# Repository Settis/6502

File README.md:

This was started as a self-educational project.
To understand how computer works I decided to create one.
The main rule here is that I should understand each bit, each connection.
I try to build it from scratch as much as possible.

I've started with a 6502 compatible CPU in Logisim [avaialbe here](/logisim/README.md).

Currently, I'm trying to build the real one around 65c816 CPU. 
As an example of how it looks you can see it working with three character displays running Wozmon:

Finally I'm able to connect all peripherals at once:

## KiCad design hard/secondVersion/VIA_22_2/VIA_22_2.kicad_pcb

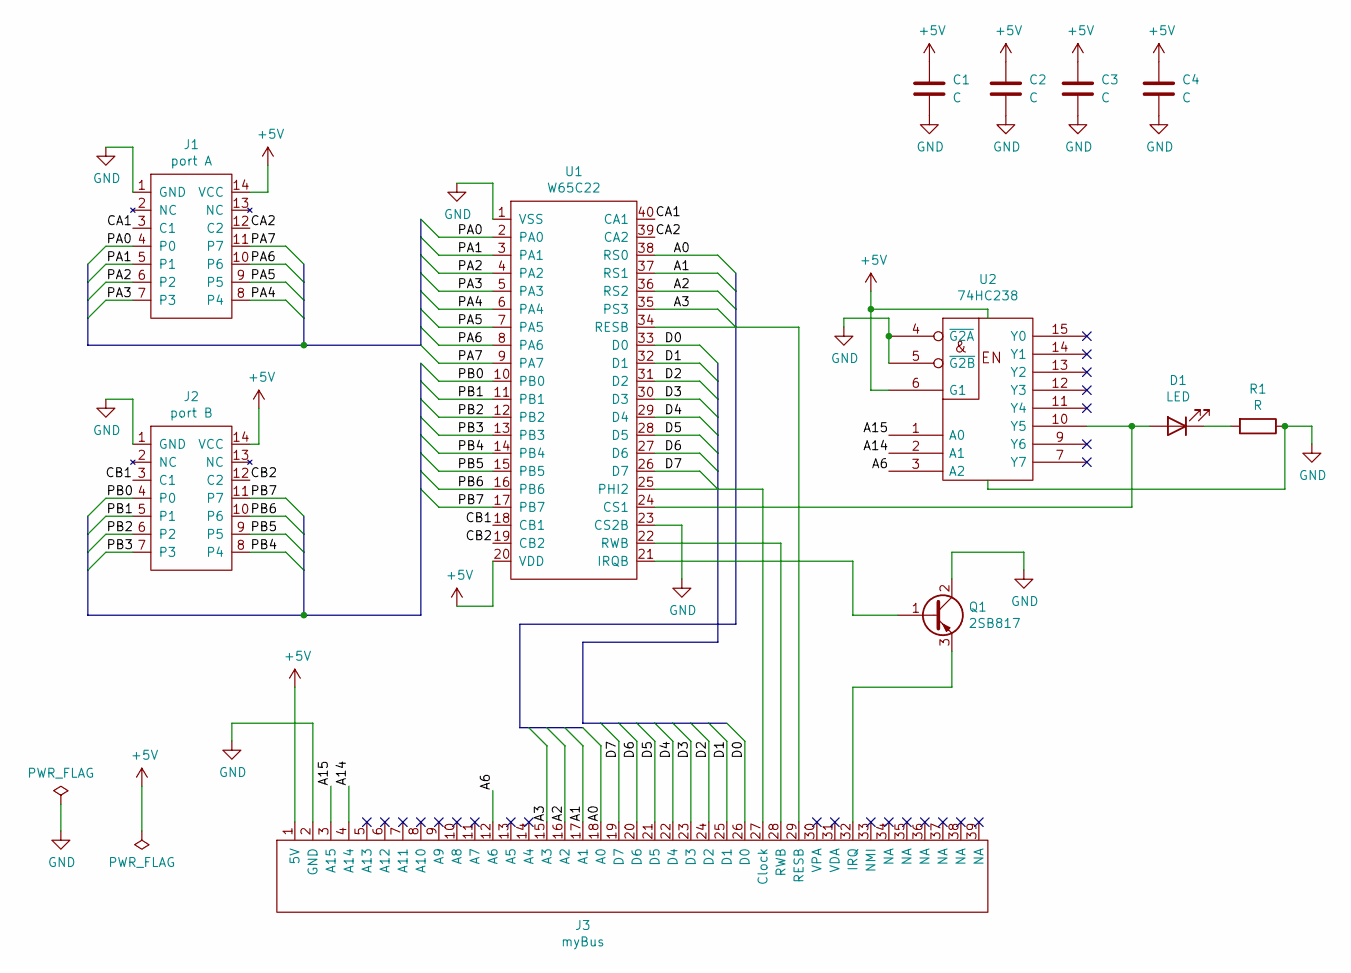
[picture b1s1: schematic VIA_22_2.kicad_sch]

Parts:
C1, C2, C3, C4: C; C_Disc_D4.3mm_W1.9mm_P5.00mm
D1: LED; LED_D5.0mm
J1: port A; DIP-14_W7.62mm_Socket
J2: port B; DIP-14_W7.62mm_Socket
J3: myBus; PinHeader_1x39_P2.54mm_Horizontal
Q1: 2SB817; TO-126-3_Vertical
R1: R; R_Axial_DIN0207_L6.3mm_D2.5mm_P15.24mm_Horizontal
U1: W65C22; DIP-40_W15.24mm_Socket
U2: 74HC238; DIP-16_W7.62mm_Socket

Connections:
/A0: J3.18 (A0), U1.38 (RS0)
/A1: J3.17 (A1), U1.37 (RS1)
/A2: J3.16 (A2), U1.36 (RS2)
/A3: J3.15 (A3), U1.35 (PS3)
/A6: J3.12 (A6), U2.3 (A2)
/A14: J3.4 (A14), U2.2 (A1)
/A15: J3.3 (A15), U2.1 (A0)
/CA1: J1.3 (C1), U1.40 (CA1)
/CA2: J1.12 (C2), U1.39 (CA2)
/CB1: J2.3 (C1), U1.18 (CB1)
/CB2: J2.12 (C2), U1.19 (CB2)
/D0: J3.26 (D0), U1.33 (D0)
/D1: J3.25 (D1), U1.32 (D1)
/D2: J3.24 (D2), U1.31 (D2)
/D3: J3.23 (D3), U1.30 (D3)
/D4: J3.22 (D4), U1.29 (D4)
/D5: J3.21 (D5), U1.28 (D5)
/D6: J3.20 (D6), U1.27 (D6)
/D7: J3.19 (D7), U1.26 (D7)
/PA0: J1.4 (P0), U1.2 (PA0)
/PA1: J1.5 (P1), U1.3 (PA1)
/PA2: J1.6 (P2), U1.4 (PA2)
/PA3: J1.7 (P3), U1.5 (PA3)
/PA4: J1.8 (P4), U1.6 (PA4)
/PA5: J1.9 (P5), U1.7 (PA5)
/PA6: J1.10 (P6), U1.8 (PA6)
/PA7: J1.11 (P7), U1.9 (PA7)
/PB0: J2.4 (P0), U1.10 (PB0)
/PB1: J2.5 (P1), U1.11 (PB1)
/PB2: J2.6 (P2), U1.12 (PB2)
/PB3: J2.7 (P3), U1.13 (PB3)
/PB4: J2.8 (P4), U1.14 (PB4)
/PB5: J2.9 (P5), U1.15 (PB5)
/PB6: J2.10 (P6), U1.16 (PB6)
/PB7: J2.11 (P7), U1.17 (PB7)
GND: C1.2, C2.2, C3.2, C4.2, J1.1 (GND), J2.1 (GND), J3.2 (GND), Q1.2 (C), R1.1, U1.1 (VSS), U1.23 (CS2B), U2.4 (~G2A), U2.5 (~G2B), U2.8 (GND)
unnamed: D1.1 (K), R1.2
unnamed: D1.2 (A), U1.24 (CS1), U2.10 (Y5)
unnamed: J3.27 (Clock), U1.25 (PHI2)
unnamed: J3.28 (RWB), U1.22 (RWB)
unnamed: J3.29 (RESB), U1.34 (RESB)
unnamed: J3.32 (IRQ), Q1.3 (E)
unnamed: Q1.1 (B), U1.21 (IRQB)

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
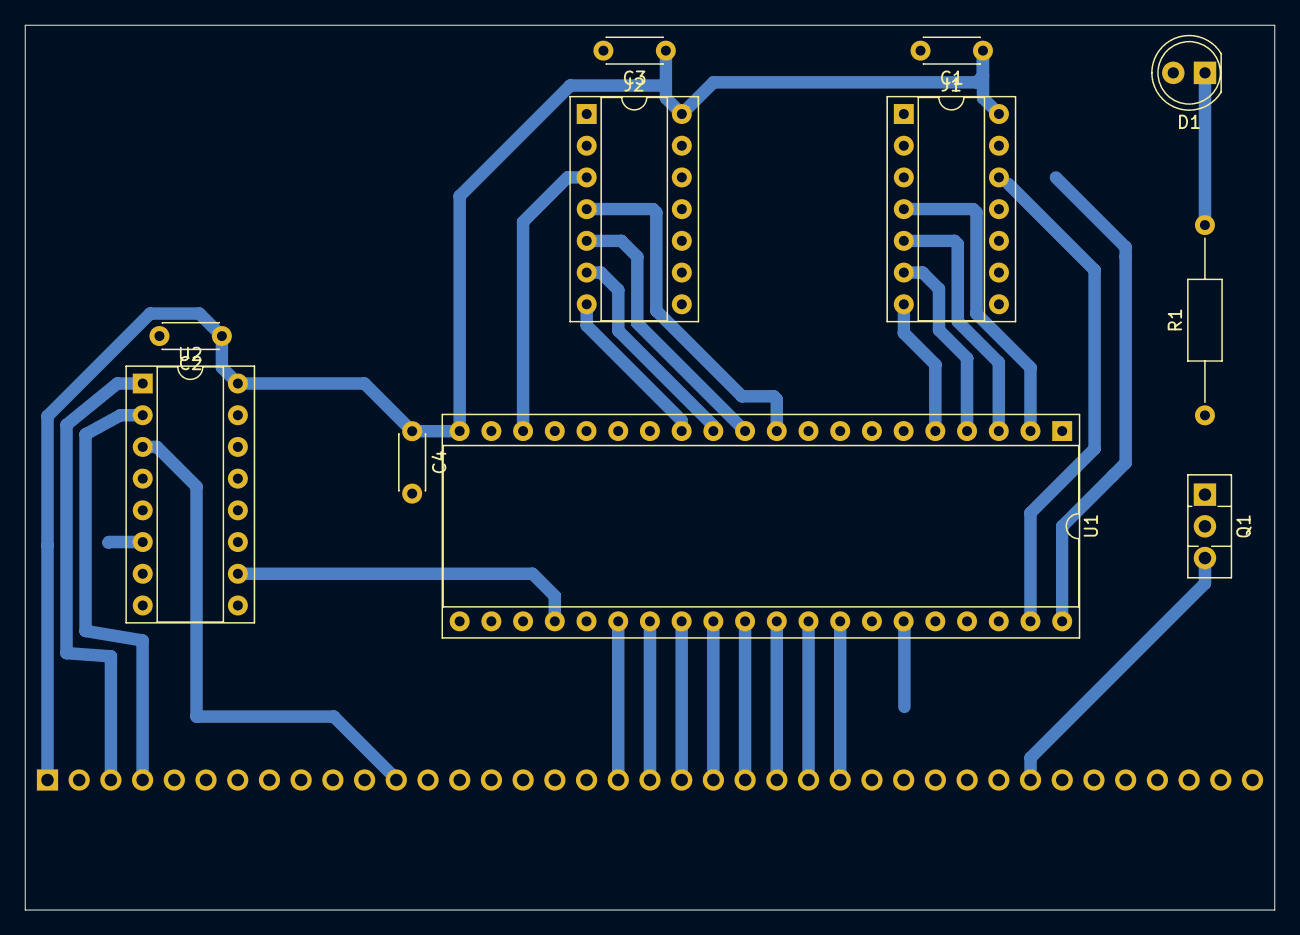
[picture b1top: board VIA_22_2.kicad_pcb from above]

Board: 2 copper layers, 100.1 x 70.9 mm, 12 parts (1 on the bottom side), 44 nets.

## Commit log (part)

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2020-01-23 Add simple commands
2020-01-24 Comp is ready.
2020-01-24 Rewrite microcode for new pins.
2020-01-24 Add and test addressing modes.
2020-01-25 Implementing some commands up to JMP.
2020-01-26 Implement all commands.
2020-01-26 Output string.
2020-01-27 Fix sub command. Test subroutine.
2020-01-27 Add images.
2020-01-27 Simple hello program. Videoadapter.
2020-01-27 Draw X code.
2020-01-28 Draw image.
2020-01-28 Gallery fixed.
2020-01-28 Image fixed.
2021-02-20 Some
2021-02-20 Couple tests
2021-03-07 CPU board initial
2021-03-07 Progs changes
2021-03-08 Add IO addr range. First workable display.
2021-03-10 Display refactored to use port handshake
2021-03-21 Something
2021-04-02 Other
2021-04-02 Two displays work
2021-04-03 Rewrite arduino part
2021-04-05 ICD impromevents
2021-04-06 Rewrite twoDisplays for right PortB pinout
2021-04-10 Try to speed up arduino
2021-04-10 Keyboard first try
2021-05-03 VIA can read port
2021-05-12 Second version of in circuit debugger
2021-06-10 Added schemas for arduino & lcd screen
2021-06-24 Start second version of hardware
2021-06-24 Add memtest
2021-07-31 ROM changes
2021-09-02 Another random commit
2021-11-15 Some updtades
2021-11-20 Updated mega Arduino things
2021-11-21 Adruino firmware ready
2021-11-26 Add port watch to ICD
2021-12-01 Display works on 5kHz
2021-12-01 Display works on 6MHz
2021-12-02 Char display works!
2021-12-04 Keyboard works. ROM standalone
2021-12-08 Debug clock
2021-12-11 Cleaning and yes program
2022-09-12 A lot of things
2022-09-12 esc & enter
2022-09-13 Pre refactoring
2022-09-13 Fix enter changing line
2022-09-14 Arrows works!
2022-09-14 backspace works
2022-09-14 type for ROM
2022-09-15 UART software echo
2022-09-15 Add UART board
2022-09-22 Board changes
2022-10-02 UART ping works
2022-10-02 ping refactored in asm
2022-10-02 Read is implemented but not works
2022-10-02 read&write works
2022-10-02 Able to read
2022-10-02 Run works
2022-10-02 Test for UART
2022-10-02 CRC works
2022-10-02 uart works in ROM
2022-10-09 Update IRQ vector after UART run programm
2022-10-30 uart6502 can be installed locally
2022-10-30 uart6502 can read & output raw data
2022-10-30 uart6502 change default write file
2022-10-30 uart6502 working with multiple pages
2022-10-30 uart6502 looks good
2022-12-04 First 3 digits!
2022-12-04 Two words mul
2022-12-04 Div works with two bytes
2022-12-04 Rename
2022-12-06 Almost! Need to test
2022-12-11 PI calc improved
2023-02-03 RTS implementation
2023-02-03 Add description to RTS
2023-02-04 Show time in ROM
2023-02-12 SD goes to idle
2023-02-19 uart6502 show logs
2023-02-19 uart6502 compile and run ability
2023-02-19 uart6502 flush each char
2023-02-19 Correct output buffer
2023-04-09 Another step
2023-04-09 Debug printing
2023-04-14 Add logging to SD card init process
2023-04-14 SD Card initialized
2023-04-15 Finally read some data
2023-09-06 Add structural macroses
2023-09-06 Fix includes in struct macro
2023-09-06 Fix display library
2023-09-06 Moving cursor on display
2023-09-07 Locomotive works
2023-09-08 Wozmon compiled
2023-09-10 Wozmon works
2023-09-10 SL integrated in Wozmon
2023-09-11 Refactor display
2023-09-12 Wozmon for ROM & readme for pyserial
2023-10-08 Update struct macro and pi readme
2023-10-08 working cc65 simple code
2023-10-08 Pi on CC65
2023-10-08 Change CPU type
2023-10-08 Add special mul10&div10 for Pi
2023-12-11 Add python script for FAT32 parsing
2024-01-14 Reading a file from FAT32
2024-01-16 Add example SD card read file output
2024-01-17 Calc resource usages
2024-01-27 Refactoring
2024-01-27 Rewriting uart test
2024-01-28 Add a sceleton for FAT testing
2024-01-31 FAT name parsing
2024-02-01 Init SD card
2024-02-02 Read sector routine
2024-02-02 Reading boot sector
2024-02-03 check boot sig
2024-02-03 logging
2024-02-03 Fix it
2024-02-04 Retry operations
2024-02-04 Read small files
2024-02-11 SD refactoring for good clock duty cycle
    There is a floating bag. Mabye with UART output.
2024-02-11 Seems still working
2024-02-19 Try to read second sector
2024-02-19 VIA 2 schematcs
2024-02-20 Reading next sectors
2024-03-13 Reading a file from sector
2024-03-13 Fix file not found
2024-03-31 First step for uart on Java
2024-04-07 Four displays
2024-04-08 Add a minimum doc
2024-04-08 Wozmon compiles again
2024-04-10 Update wozmon to support 3 displays
2024-04-11 Update steam locomotive
2024-05-26 Update uart6502
    It don't show stacktrace that often.
    Non printable characters printed in hex.
2024-05-26 Fix loop over test files
2024-05-26 Some helpers
2024-06-01 Multicluster files support
2024-06-01 Calc running time for uart6502
2024-06-04 Add running time
2024-06-12 SD works via shift register
2024-06-19 Try to make it work with VIA shift
2024-07-01 Revert "SD works via shift register"
    This reverts commit 81c780824f7c37b000026dad384286bfc184f042.
2024-07-01 SD card bit banging works
2024-07-03 Add at least some deiscriptions
2024-07-03 Folder renaming
2024-07-05 Shematics refactoring
2024-07-05 Fix errors in schematics
2024-07-05 Add echo for symon
2024-07-05 Update sd adapter schematic
2024-07-06 SD works via shift register
    (cherry picked from commit 81c780824f7c37b000026dad384286bfc184f042)
2024-07-10 read numbers
2024-07-11 Simple commands
2024-07-11 Execute works properly
2024-07-13 Constant definition
2024-07-13 Constant creation refactoring
2024-07-13 Add variable word
2024-07-13 DP & STATE variables
2024-07-14 Docol do nothing
2024-07-14 Compling but not running
2024-07-18 words works!
2024-07-18 All words updated
2024-07-18 Compile literals
2024-07-20 SD shift based on interrupt
2024-07-20 Speed up a little
2024-07-20 Speed up SD card
2024-07-21 Bootloader ready
2024-07-23 Demo for MCM
2024-07-24 Preparing for Forth programming
    Stripper for clean Forth of comment, newlines, etc.
    Check for numbers in order to fail on unknown words.
    Bring debug flags in one place.
2024-07-25 SD speeded
2024-07-27 Update bootloader with the latest SD lib version
2024-07-28 forth if half-works
2024-07-31 Fix stripper and implementing if
2024-08-01 IF with errors checking
2024-08-01 BEGIN implementation
2024-08-04 LOOP works
    As well as I and LEAVE.
    FIX NAN logic.
2024-08-04 +LOOP works
2024-08-05 Clean stacks for debug
2024-10-05 Work with string literals
2024-10-06 Interpreter works
2024-10-17 Compilation almost works
2024-10-18 Literals compilation
2024-10-18 Multiline definitions
2024-10-18 Constant & variables work
2024-10-27 Differentiate interrupts
2024-10-28 Try to use 6522 timer
2024-11-02 Connection via WiFi
2024-11-17 uart6502 v0.6.0
    Allow to connect via network
2024-11-30 Update shematics for UART & ESP
2024-11-30 Add another WiFi to ESP
2024-12-03 Use the real hardware instead of symon
    Symon claimed that it implemented VIA chip, but it is not.
2024-12-03 Creating Forth bench
2024-12-04 Bubble sort
2024-12-04 Forth with hardware return stack
2024-12-11 Start to implement FORTH with native calls
2024-12-12 Forth with compiler
    CONSTANT, VARIABLE and !, @ works
2024-12-13 Native FORTH compiler works
2024-12-14 Native forth compile literals
2024-12-14 FORTH native branches
    Branches works with absolute address
2024-12-14 FORTH native EXECUTE
2024-12-15 Native FORTH prints invitation
2024-12-15 Forth native benchmark
2024-12-16 Implement yet another FOTH
2024-12-17 Renaming to Marcus
2024-12-19 Set longer timeout
    But it didn't help
2025-01-25 Wozmon for 1 display
2025-01-26 Add UART and CharDisplay libs
2025-01-30 Update Arduino python script
    For dump whole ROM.
2025-01-30 EEPROM writer
    Now I can update EEPROM without Arduino
2025-02-01 First ADR
    Especially right now, when I start to change things, I have to document my thoughts.
2025-02-01 Write ROM in pages
2025-02-01 Update ROM design
2025-02-02 Add more ADR's
2025-02-09 Add 3D model
2025-02-09 Fix 65816 std for IND16
2025-02-10 Speed up UART
2025-02-11 uart6502 supports atari files
2025-02-12 Create a build script
2025-02-12 Update uart6502 compile&run
2025-02-13 Update build script
    Now it takes into account included files
2025-02-18 Started FORTH implementation
    As well as simple FORTH compiler
2025-02-20 Implement some FORTH low level words
2025-02-21 [FORTH compiler] Literal and IF support
2025-02-21 Add ADRs
2025-02-23 FORTH (FIND)
2025-02-26 FORTH compiler control structures support
2025-02-26 FORTH DO-LOOP
2025-02-26 Renaming
2025-02-26 FORTH DOCON & DOVAR
2025-02-26 FORTH user variables
2025-03-02 Move IO buffer upper
2025-03-03 Steps toward UART
2025-03-04 Update some files
2025-03-07 Fix spurious interrupts
2025-03-08 Fix reset vector
2025-03-08 FORTH via UART
2025-03-12 Send file to UART
2025-03-13 Forth output string literals
2025-03-16 FORTH interpreter
    Execute commands and pring HEX number
2025-03-17 FORTH Simple number input
2025-03-17 FORTH fix error word
2025-03-17 FORTH convert UART to upper case
2025-03-17 FORTH error messages
2025-03-17 Update FORTH compiler
    to show error in string literal parsing
2025-03-18 FORTH sompilation, var & const
2025-03-18 FORTH code blocks
2025-03-18 FORTH string literal
2025-03-18 Reset UART
2025-03-18 FORTH ignore comments
2025-03-18 FORTH some fixes
2025-03-19 Fix uart6502 script sending
2025-03-19 FORTH testing works!
2025-03-20 FORTH Double layout in stack
2025-03-20 FORTH display work
2025-03-21 uart6502 several script files
2025-03-21 FORTH test
2025-03-22 FORTH fix stack check
    delete auto upper case
    enable interrupts after variables are prepared
2025-03-22 uart6502 send script fix
    Wait for 6502 invitation before sending script content
2025-03-22 Import-export some FORTH pseudo regs
2025-03-22 FORTH fix comment cut
2025-05-15 Add music test
2025-05-18 Music
2025-05-19 Fix music timings
2025-05-20 Multiple channels
    and timing fix
2025-05-21 Implement music player
2025-05-23 Add some FORTH tests
2025-05-24 Add more ADR
2025-05-30 Division
2025-05-31 FORTH '.' impmelentation
2025-06-01 FORTH DMINUS rewrite
2025-06-01 FORTH Number convertion
2025-06-01 FORTH number with BASE recognition
2025-06-01 FORTH tests runs till the end
2025-06-01 FORTH uptime ms output
2025-06-02 FORTH test fixes
2025-06-02 Another FORTH test improvement
2025-06-02 FORTH core test
2025-06-22 Add FORTH core words
2025-07-03 FORTH test fix
2025-07-03 Update schematics for latest KiCad
2025-07-21 Update schematics for peripherals
2025-07-23 Update schematics pin numbers
2025-07-26 Update schematics with audio amplifier
2025-07-26 FORTH with display and keyboard
2025-07-27 Fix keyboard scancodes read
2025-07-29 Write FORTH to ROM
2025-08-16 Change SD error
2025-08-17 FORTH open fat files in root
2025-09-02 Update UART schematics for flow control
2025-09-16 new UART support
    fix schematics by adding a resistor
    renaming PC/2 to correct PS/2
    Updating FORTH to detect terminal connection
2025-09-30 Display & keyboard from peripherals board
    As well as fixing wrong soldering.
2025-10-02 SD card works
2025-10-02 RUN 4th files
2025-10-21 Fix UART pullup
2025-10-22 Fix UART monitor to work with data carrier pin
2025-10-22 Add peritherals
2025-11-06 Add volume words
2025-12-17 WIP
    It's still not working, but it's better to commit.
2025-12-17 Periferals
2025-12-28 Adruino breakpoint support
2025-12-28 Dirty fix for compiling
2026-02-02 Debugger initial implementation
2026-02-07 Fixed uart monitor interrup and stack
2026-02-08 uart6502 fix
    Update opcodes. Fix args parsing.
2026-02-14 [ADR] 0009 same uart6502 for Arduio
2026-02-14 [ADR] 0010 Disable Arduino autoreboot
2026-02-14 [ADR] 0011 autodetect peripherals
2026-02-16 Some fix
2026-02-17 FORTH compiler creates scope for CODE
2026-02-18 Check periperals connected
2026-03-30 Forth fix
2026-06-05 Add resistor to clock in peripherals board
2026-06-05 Add waiting for RTC
2026-06-05 Some tweaks for UART Flow control
    It works, but not reliably. I'd rather delete it.
2026-06-05 Reprint schematics
2026-06-05 Add ADR-0012 UART backpressure
2026-06-05 Add ADR-0013 UART interrupt
2026-06-10 Fix RTC
2026-06-11 Draw reset board
2026-06-12 Add TTL VGA schematics
2026-06-17 Read/Write RTC
2026-06-18 Print date
2026-06-23 Fix uart6502 type command
2026-06-23 Add some music
2026-06-23 Update date word
2026-06-23 Add BC game
2026-06-23 Update FORTH examples
2026-06-25 Some fixes
